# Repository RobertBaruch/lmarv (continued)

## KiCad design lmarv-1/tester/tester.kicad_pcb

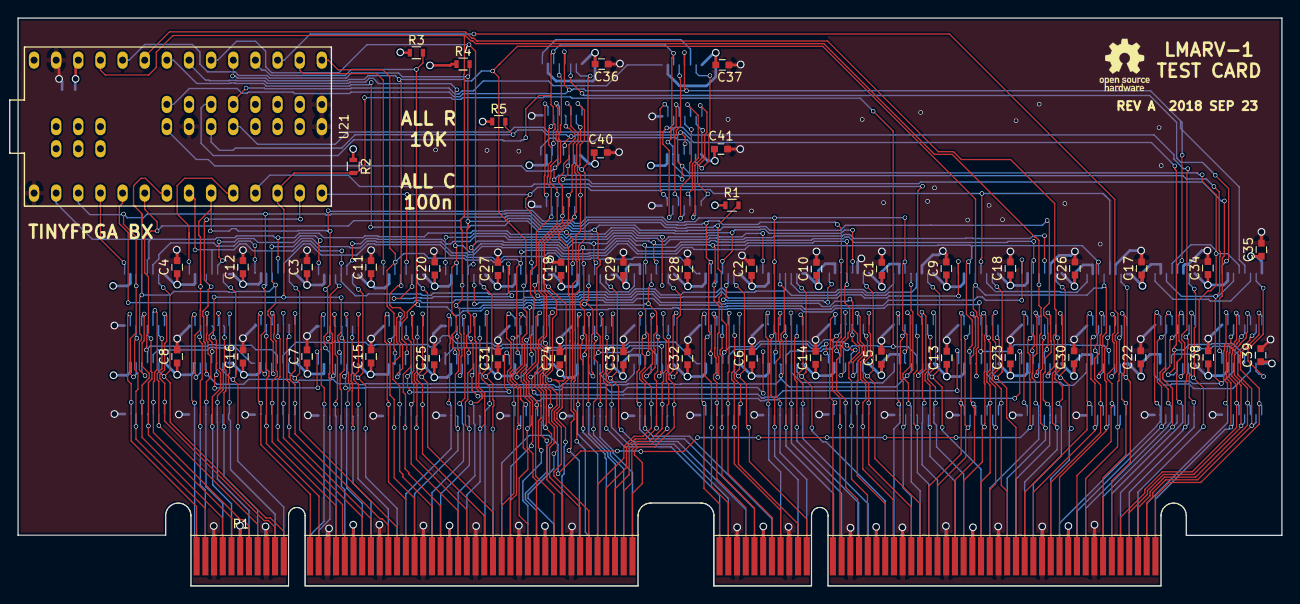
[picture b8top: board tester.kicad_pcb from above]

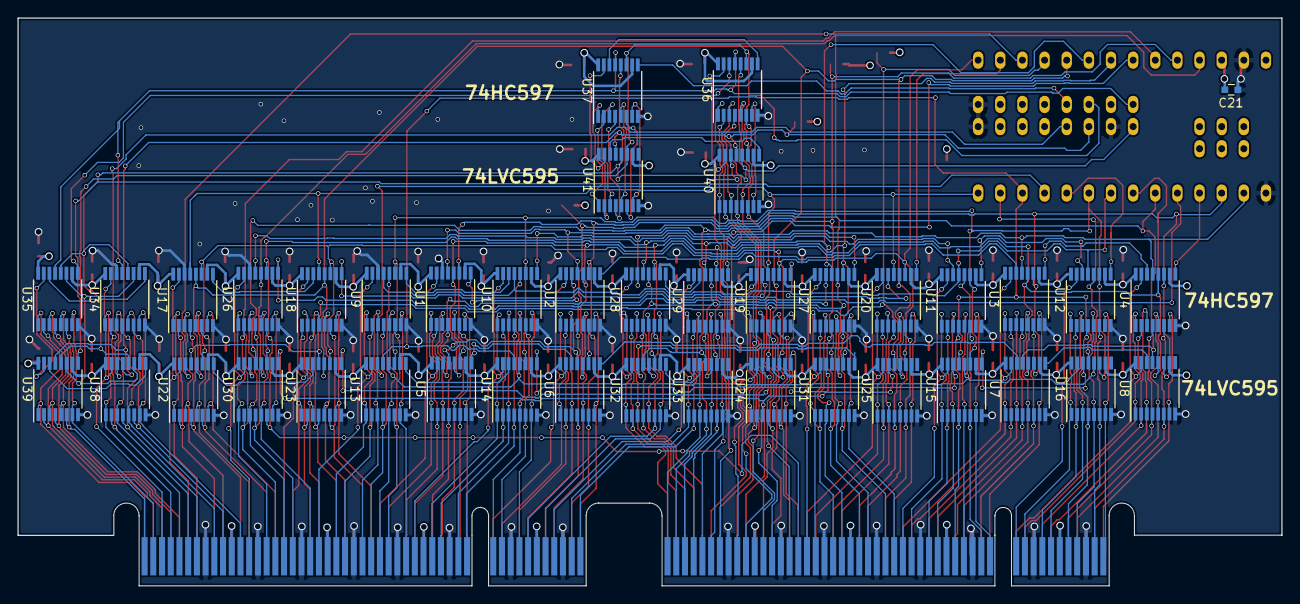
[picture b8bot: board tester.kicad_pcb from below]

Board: 4 copper layers, 145.0 x 65.1 mm, 88 parts (41 on the bottom side), 222 nets.

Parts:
C1, C2, C3, C4, C5, C6, C7, C8, C9, C10, C11, C12, C13, C14, C15, C16, C17, C18, C19, C20, C21, C22, C23, C24, C25, C26, C27, C28, C29, C30, C31, C32, C33, C34, C35, C36, C37, C38, C39, C40, C41: 0u1; C_0603
P1: dual-pcie-cardedge; PCI-EXPRESS
R1, R2, R3, R4, R5: 10k; R_0603
U1, U2, U3, U4, U9, U10, U11, U12, U17, U18, U19, U20, U26, U27, U28, U29, U34, U35, U36, U37: 74HC597; TSSOP-16_4.4x5mm_Pitch0.65mm
U5, U6, U7, U8, U13, U14, U15, U16, U22, U23, U24, U25, U30, U31, U32, U33, U38, U39, U40, U41: 74LVC595; TSSOP-16_4.4x5mm_Pitch0.65mm
U21: TinyFPGA_BX

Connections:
/BOOT_CLK: P1.194, U34.15, U38.15
/CCLK: U21.48, U34.11, U35.11, U36.11, U37.11, U38.11, U39.11, U40.11, U41.11
/CRS0: U34.9, U35.14
/CRS1: U35.9, U36.14
/CRS2: U36.9, U37.14
/CSI: U21.38, U38.14
/CSO: U21.47, U37.9
/CWLD: U21.35, U34.12, U35.12, U36.12, U37.12, U38.12, U39.12, U40.12, U41.12
/CWS0: U38.9, U39.14
/CWS1: U39.9, U40.14
/CWS2: U40.9, U41.14
/RCCLK: U21.21, U26.11, U27.11, U28.11, U29.11, U30.11, U31.11, U32.11, U33.11
/RCRS0: U26.9, U27.14
/RCRS1: U27.9, U28.14
/RCRS2: U28.9, U29.14
/RCSI: U21.23, U30.14
/RCSO: U21.22, U29.9
/RCWLD: U21.25, U26.12, U27.12, U28.12, U29.12, U30.12, U31.12, U32.12, U33.12
/RCWS0: U30.9, U31.14
/RCWS1: U31.9, U32.14
/RCWS2: U32.9, U33.14
/RDCLK: U1.11, U2.11, U3.11, U4.11, U5.11, U6.11, U7.11, U8.11, U21.3
/RDRS0: U1.9, U2.14
/RDRS1: U2.9, U3.14
/RDRS2: U3.9, U4.14
/RDSI: U5.14, U21.5
/RDSO: U4.9, U21.4
/RDWLD: U1.12, U2.12, U3.12, U4.12, U5.12, U6.12, U7.12, U8.12, U21.7
/RDWS0: U5.9, U6.14
/RDWS1: U6.9, U7.14
/RDWS2: U7.9, U8.14
/RS1CLK: U9.11, U10.11, U11.11, U12.11, U13.11, U14.11, U15.11, U16.11, U21.9
/RS1RS0: U9.9, U10.14
/RS1RS1: U10.9, U11.14
/RS1RS2: U11.9, U12.14
/RS1SI: U13.14, U21.11
/RS1SO: U12.9, U21.10
/RS1WLD: U9.12, U10.12, U11.12, U12.12, U13.12, U14.12, U15.12, U16.12, U21.13
/RS1WS0: U13.9, U14.14
/RS1WS1: U14.9, U15.14
/RS1WS2: U15.9, U16.14
/RS2CLK: U17.11, U18.11, U19.11, U20.11, U21.15, U22.11, U23.11, U24.11, U25.11
/RS2RS0: U17.9, U18.14
/RS2RS1: U18.9, U19.14
/RS2RS2: U19.9, U20.14
/RS2SI: U21.17, U22.14
/RS2SO: U20.9, U21.16
/RS2WLD: U17.12, U18.12, U19.12, U20.12, U21.19, U22.12, U23.12, U24.12, U25.12
/RS2WS0: U22.9, U23.14
/RS2WS1: U23.9, U24.14
/RS2WS2: U24.9, U25.14
/f[0]: P1.188, U34.5, U38.5
/f[1]: P1.190, U34.4, U38.4
/f[2]: P1.191, U34.3, U38.3
/f[3]: P1.192, U34.2, U38.2
/nc[0]: P1.133, U36.6, U40.6
/nc[1]: P1.135, U36.5, U40.5
/nc[2]: P1.136, U36.4, U40.4
/nc[3]: P1.138, U36.3, U40.3
/nc[4]: P1.139, U36.2, U40.2
/nc[5]: P1.141, U36.1, U40.1
/nc[6]: P1.142, U36.15, U40.15
/nc[7]: P1.94, U35.5, U39.5
/nc[8]: P1.95, U35.4, U39.4
/nc[9]: P1.96, U35.3, U39.3
/nc[10]: P1.97, U35.2, U39.2
/nc[11]: P1.98, U35.1, U39.1
/q0: U26.7, U30.7
/q1: U28.15, U32.15
/q2: U35.15, U39.15
/q3: U36.7, U40.7
/q4: U37.15, U41.15
/q5: U37.1, U41.1
/q6: U37.2, U41.2
/q7: U37.3, U41.3
/q8: U37.4, U41.4
/q9: U37.5, U41.5
/q10: U37.6, U41.6
/q11: U37.7, U41.7
/rd[0]: P1.71, U1.15, U5.15
/rd[1]: P1.70, U1.1, U5.1
/rd[2]: P1.68, U1.2, U5.2
/rd[3]: P1.67, U1.3, U5.3
/rd[4]: P1.65, U1.4, U5.4
/rd[5]: P1.64, U1.5, U5.5
/rd[6]: P1.62, U1.6, U5.6
/rd[7]: P1.61, U1.7, U5.7
/rd[8]: P1.60, U2.15, U6.15
/rd[9]: P1.59, U2.1, U6.1
/rd[10]: P1.57, U2.2, U6.2
/rd[11]: P1.56, U2.3, U6.3
/rd[12]: P1.54, U2.4, U6.4
/rd[13]: P1.53, U2.5, U6.5
/rd[14]: P1.51, U2.6, U6.6
/rd[15]: P1.50, U2.7, U6.7
/rd[16]: P1.22, U3.15, U7.15
/rd[17]: P1.21, U3.1, U7.1
/rd[18]: P1.19, U3.2, U7.2
/rd[19]: P1.18, U3.3, U7.3
/rd[20]: P1.16, U3.4, U7.4
/rd[21]: P1.15, U3.5, U7.5
/rd[22]: P1.13, U3.6, U7.6
/rd[23]: P1.12, U3.7, U7.7
/rd[24]: P1.11, U4.15, U8.15
/rd[25]: P1.10, U4.1, U8.1
/rd[26]: P1.8, U4.2, U8.2
/rd[27]: P1.7, U4.3, U8.3
/rd[28]: P1.5, U4.4, U8.4
/rd[29]: P1.4, U4.5, U8.5
/rd[30]: P1.2, U4.6, U8.6
/rd[31]: P1.1, U4.7, U8.7
/rda[0]: P1.45, U28.5, U32.5
/rda[1]: P1.46, U28.4, U32.4
/rda[2]: P1.47, U28.3, U32.3
/rda[3]: P1.48, U28.2, U32.2
/rda[4]: P1.49, U28.1, U32.1
/rs1[0]: P1.176, U9.15, U13.15
/rs1[1]: P1.174, U9.1, U13.1
/rs1[2]: P1.173, U9.2, U13.2
/rs1[3]: P1.171, U9.3, U13.3
/rs1[4]: P1.170, U9.4, U13.4
/rs1[5]: P1.169, U9.5, U13.5
/rs1[6]: P1.168, U9.6, U13.6
/rs1[7]: P1.166, U9.7, U13.7
/rs1[8]: P1.165, U10.15, U14.15
/rs1[9]: P1.163, U10.1, U14.1
/rs1[10]: P1.162, U10.2, U14.2
/rs1[11]: P1.160, U10.3, U14.3
/rs1[12]: P1.159, U10.4, U14.4
/rs1[13]: P1.158, U10.5, U14.5
/rs1[14]: P1.157, U10.6, U14.6
/rs1[15]: P1.155, U10.7, U14.7
/rs1[16]: P1.120, U11.15, U15.15
/rs1[17]: P1.119, U11.1, U15.1
/rs1[18]: P1.117, U11.2, U15.2
/rs1[19]: P1.116, U11.3, U15.3
/rs1[20]: P1.114, U11.4, U15.4
/rs1[21]: P1.113, U11.5, U15.5
/rs1[22]: P1.111, U11.6, U15.6
/rs1[23]: P1.110, U11.7, U15.7
/rs1[24]: P1.109, U12.15, U16.15
/rs1[25]: P1.108, U12.1, U16.1
/rs1[26]: P1.106, U12.2, U16.2
/rs1[27]: P1.105, U12.3, U16.3
/rs1[28]: P1.103, U12.4, U16.4
/rs1[29]: P1.102, U12.5, U16.5
/rs1[30]: P1.100, U12.6, U16.6
/rs1[31]: P1.99, U12.7, U16.7
/rs1a[0]: P1.154, U28.6, U32.6
/rs1a[1]: P1.152, U28.7, U32.7
/rs1a[2]: P1.151, U29.15, U33.15
/rs1a[3]: P1.149, U29.1, U33.1
/rs1a[4]: P1.148, U29.2, U33.2
/rs2[0]: P1.93, U17.15, U22.15
/rs2[1]: P1.92, U17.1, U22.1
/rs2[2]: P1.90, U17.2, U22.2
/rs2[3]: P1.89, U17.3, U22.3
/rs2[4]: P1.87, U17.4, U22.4
/rs2[5]: P1.86, U17.5, U22.5
/rs2[6]: P1.84, U17.6, U22.6
/rs2[7]: P1.83, U17.7, U22.7
/rs2[8]: P1.82, U18.15, U23.15
/rs2[9]: P1.81, U18.1, U23.1
/rs2[10]: P1.79, U18.2, U23.2
/rs2[11]: P1.78, U18.3, U23.3
/rs2[12]: P1.76, U18.4, U23.4
/rs2[13]: P1.75, U18.5, U23.5
/rs2[14]: P1.73, U18.6, U23.6
/rs2[15]: P1.72, U18.7, U23.7
/rs2[16]: P1.44, U19.15, U24.15
/rs2[17]: P1.43, U19.1, U24.1
/rs2[18]: P1.41, U19.2, U24.2
/rs2[19]: P1.40, U19.3, U24.3
/rs2[20]: P1.38, U19.4, U24.4
/rs2[21]: P1.37, U19.5, U24.5
/rs2[22]: P1.35, U19.6, U24.6
/rs2[23]: P1.34, U19.7, U24.7
/rs2[24]: P1.33, U20.15, U25.15
/rs2[25]: P1.32, U20.1, U25.1
/rs2[26]: P1.30, U20.2, U25.2
/rs2[27]: P1.29, U20.3, U25.3
/rs2[28]: P1.27, U20.4, U25.4
/rs2[29]: P1.26, U20.5, U25.5
/rs2[30]: P1.24, U20.6, U25.6
/rs2[31]: P1.23, U20.7, U25.7
/rs2a[0]: P1.147, U29.3, U33.3
/rs2a[1]: P1.146, U29.4, U33.4
/rs2a[2]: P1.145, U29.5, U33.5
/rs2a[3]: P1.144, U29.6, U33.6
/rs2a[4]: P1.143, U29.7, U33.7
/~BOOT_ALU_EN: P1.193, U34.1, U38.1
/~BOOT_RST: P1.195, U35.7, U39.7
/~BOOT_WR: P1.196, U35.6, U39.6
/~COE: R5.2, U21.37, U38.13, U39.13, U40.13, U41.13
/~CRLD: U21.50, U34.13, U35.13, U36.13, U37.13
/~RCOE: R4.2, U21.24, U30.13, U31.13, U32.13, U33.13
/~RCRLD: U21.20, U26.13, U27.13, U28.13, U29.13
/~RDOE: R1.2, U5.13, U6.13, U7.13, U8.13, U21.6
/~RDRLD: U1.13, U2.13, U3.13, U4.13, U21.2
/~RS1OE: R2.2, U13.13, U14.13, U15.13, U16.13, U21.12
/~RS1RLD: U9.13, U10.13, U11.13, U12.13, U21.8
/~RS2OE: R3.2, U21.18, U22.13, U23.13, U24.13, U25.13
/~RS2RLD: U17.13, U18.13, U19.13, U20.13, U21.14
/~alu_oe: P1.187, U34.6, U38.6
/~rd_bhh: P1.121, U27.7, U31.7
/~rd_bhl: P1.122, U27.6, U31.6
/~rd_blh: P1.177, U26.5, U30.5
/~rd_bll: P1.179, U26.4, U30.4
/~rd_wr: P1.124, U27.5, U31.5
/~rs1_bhh: P1.130, U27.1, U31.1
/~rs1_bhl: P1.131, U27.15, U31.15
/~rs1_blh: P1.182, U26.1, U30.1
/~rs1_bll: P1.184, U26.15, U30.15
/~rs1_rd: P1.132, U26.6, U30.6
/~rs2_bhh: P1.125, U27.4, U31.4
/~rs2_bhl: P1.127, U27.3, U31.3
/~rs2_blh: P1.180, U26.3, U30.3
/~rs2_bll: P1.181, U26.2, U30.2
/~rs2_rd: P1.128, U27.2, U31.2
/~shift_oe: P1.185, U34.7, U38.7
GND: C1.2, C2.2, C3.2, C4.2, C5.2, C6.2, C7.2, C8.2, C9.2, C10.2, C11.2, C12.2, C13.2, C14.2, C15.2, C16.2, C17.2, C18.2, C19.2, C20.2, C21.2, C22.2, C23.2, C24.2, C25.2, C26.2, C27.2, C28.2, C29.2, C30.2, C31.2, C32.2, C33.2, C34.2, C35.2, C36.2, C37.2, C38.2, C39.2, C40.2, C41.2, P1.3, P1.9, P1.14, P1.20, P1.25, P1.31, P1.36, P1.42, P1.52, P1.58, P1.63, P1.69, P1.74, P1.80, P1.85, P1.91, P1.101, P1.107, P1.112, P1.118, P1.123, P1.129, P1.134, P1.140, P1.150, P1.156, P1.161, P1.167, P1.172, P1.178, P1.183, P1.189, U1.8, U1.14, U2.8, U3.8, U4.8, U5.8, U6.8, U7.8, U8.8, U9.8, U9.14, U10.8, U11.8, U12.8, U13.8, U14.8, U15.8, U16.8, U17.8, U17.14, U18.8, U19.8, U20.8, U21.1, U21.27, U21.36, U21.42, U21.43, U22.8, U23.8, U24.8, U25.8, U26.8, U26.14, U27.8, U28.8, U29.8, U30.8, U31.8, U32.8, U33.8, U34.8, U34.14, U35.8, U36.8, U37.8, U38.8, U39.8, U40.8, U41.8
VCC: C1.1, C2.1, C3.1, C4.1, C5.1, C6.1, C7.1, C8.1, C9.1, C10.1, C11.1, C12.1, C13.1, C14.1, C15.1, C16.1, C17.1, C18.1, C19.1, C20.1, C21.1, C22.1, C23.1, C24.1, C25.1, C26.1, C27.1, C28.1, C29.1, C30.1, C31.1, C32.1, C33.1, C34.1, C35.1, C36.1, C37.1, C38.1, C39.1, C40.1, C41.1, P1.6, P1.17, P1.28, P1.39, P1.55, P1.66, P1.77, P1.88, P1.104, P1.115, P1.126, P1.137, P1.153, P1.164, P1.175, P1.186, R1.1, R2.1, R3.1, R4.1, R5.1, U1.10, U1.16, U2.10, U2.16, U3.10, U3.16, U4.10, U4.16, U5.10, U5.16, U6.10, U6.16, U7.10, U7.16, U8.10, U8.16, U9.10, U9.16, U10.10, U10.16, U11.10, U11.16, U12.10, U12.16, U13.10, U13.16, U14.10, U14.16, U15.10, U15.16, U16.10, U16.16, U17.10, U17.16, U18.10, U18.16, U19.10, U19.16, U20.10, U20.16, U21.26, U22.10, U22.16, U23.10, U23.16, U24.10, U24.16, U25.10, U25.16, U26.10, U26.16, U27.10, U27.16, U28.10, U28.16, U29.10, U29.16, U30.10, U30.16, U31.10, U31.16, U32.10, U32.16, U33.10, U33.16, U34.10, U34.16, U35.10, U35.16, U36.10, U36.16, U37.10, U37.16, U38.10, U38.16, U39.10, U39.16, U40.10, U40.16, U41.10, U41.16

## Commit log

2018-01-22 Initial dump
2018-02-08 Updated register card and breakout
2018-05-30 Adds RAM-based register card
2018-05-30 Updates silkscreen and gerbers for register card
2018-07-08 Dump for backing up, 2018 Jul 7
2018-08-10 Adds tinyfpga test things
2018-10-13 Mainly updates alu.py simulator
2018-10-22 Update alu.py, add some instruction diagrams
2018-10-24 Add BitPattern generator.
2018-10-27 bit_pattern: use lower case for function name
2018-10-27 alu.py: Add TODOs
2018-10-27 Add lmarv-1/utils.py
2018-10-27 Add lmarv-1/test_runner.py
2018-10-28 Remove test_runner.py
2018-10-28 Add alu_test.py
2018-10-28 alu_test.py: add more functions.
2018-10-28 Updated ALU, tester, more instruction pages
2018-11-08 Add lmarv-1/tester_v2.py: but not tested yet
2018-11-14 add passthru_tester.py: but not tested yet.
2018-11-14 Update tester/alu boards, adds instructions book
2018-11-27 Make PCA9698DDG working.
    * Fixed the i2c address of the last PCA9698DDG.
    * Fixed wrong register names for output
    * Move reset to the beginning.
2018-11-27 .gitignore: add vim temp files and .pyc
2018-12-16 Updates tester, alu, adds lights-n-jumpers, ht1632 breakout
2018-12-16 Alters testing programs
2019-01-28 ALU rev D, with simulations
2021-04-14 Add LICENSE file
